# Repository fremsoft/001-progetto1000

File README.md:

# #progetto1000 il Robot che risolve il Cubo di Rubik
Questo è il primo progetto del [:arrow_forward: Canale YouTube "PROGETTI con Emanuele Frisoni"](https://youtube.com/c/fremsoft), un progetto collaborativo che nasce al raggiungimento di 1000 iscritti: [:movie_camera: Guarda la Playlist completa del progetto](https://www.youtube.com/watch?v=VcB0eAnL97o&list=PLxAafib4pWc7LSfuXC9RSEif6I1dyx5FP)

1. [Parte la progettazione in Live Streaming su Twitch](README.md#parte-la-progettazione-in-live-streaming-su-twitch)
2. [Definizione delle specifiche](README.md#definizione-delle-specifiche)
3. [Attività da svolgere e svolte](README.md#attivit%C3%A0-da-svolgere-e-svolte)
4. [Codici sorgenti](README.md#codici-sorgenti)
5. [Sostieni PROGETTO1000](README.md#sostieni-progetto1000)
6. [Lista della spesa](README.md#lista-della-spesa)

   6.1 [Attrezzature da laboratorio e Kit](README.md#attrezzature-da-laboratorio-e-kit)
   
   6.2 [Materiale e schede elettroniche](README.md#materiale-e-schede-elettroniche)
   
   6.3 [Materiale vario per assemblaggio prototipo](README.md#materiale-vario-per-assemblaggio-prototipo)

## Parte la progettazione in Live Streaming su Twitch
**Ogni Giovedì sera alle 22:00** ci incontriamo su [Twitch Tv](https://www.twitch.tv/fremsoft) per progettare insieme il Robot che risolve il Cubo di Rubik, partendo da zero. Affronteremo tutti i passaggi in maniera approfondita. Ho deciso di utilizzare tecnologie che conosco "per sentito dire", ma su cui non ho mai lavorato. In questo modo vedrai tutto il processo che sta dietro alla ricerca di una soluzione. A differenza di altri progetti che trovi in rete, #progetto1000 non esiste ancora, lo possiamo creare insieme. 

Lo scopo non è mostrare al mondo quanto siamo bravi, ma mostrare agli aspiranti progettisti quali sono tutte le difficoltà che potranno incontrare nel loro percorso e suggerire un modo per affrontarle e superarle.

:clapper: Canale Twitch:  [https://www.twitch.tv/fremsoft](https://www.twitch.tv/fremsoft)

[^ Torna su](README.md#progetto1000-il-robot-che-risolve-il-cubo-di-rubik)

## Definizione delle specifiche
Siccome si tratta di un progetto collaborativo, per definire le specifiche di progetto sono stati fatti alcuni sondaggi esplorativi per determinare quali tecnologie utilizzare in questo primo progetto. I risultati del sondaggio sono i seguenti:

1. Arduino o Microchip PIC? **ARDUINO** [4 voti / 2]

2. Encoder Ottico o Accelerometro Gravitazionale? **ENCODER OTTICO** [3 voti / 1]

3. Costruzioni LEGO o Particolari stampati con Stampante 3D? **STAMPA 3D** [3 voti / 4]

4. Stand alone o Connesso a un PC/Smartphone? **SIA STANDALONE CHE COMANDATO** [4 voti / 4]

5. Muto o Sonoro? **SONORO** [3 voti / 4]

6. Cieco o con Telecamera? **TELECAMERA** [0 voti / 4]

7. Procedurale o Intelligenza Artificiale? **A.I.** [0 voti / 5 ]

[^ Torna su](README.md#progetto1000-il-robot-che-risolve-il-cubo-di-rubik)

## Attività da svolgere e svolte
Ogni progetto che si rispetti deve prevedere una serie di fasi da svolgere. Maggiore sarà la difficoltà del progetto e maggiori sono le incognite, tanto più sarà difficile riuscire a prevedere con esattezza tutte le fasi. Ciononostante, è sempre buona norma prevedere con la massima accuratezza tutte le fasi del progetto in una sorta di planning. Ad ogni modo il progetto può essere periodicamente rivisitato, modificato e corretto, in corso d'opera.

L'utilità di suddividere il progetto in attività elementari, consente al progettista di avere un approccio più razionale ed evitare di disperdersi. Inoltre, laddove sia possibile lavorare in Team, la suddivisione del progetto in attività consente di stabilire se alcune attività possano essere svolte simultaneamente da più attori, per esempio dopo aver definito le specifiche di progetto con precisione, si può affidare il progetto meccanico ad un Team ed il progetto elettronico ad un altro Team di sviluppatori.

- [x] [Analisi di fattibilità](https://youtu.be/We6UntzGp7k)
- [x] Raccolta della documentazione e prove sperimentali con prototipi
  - [x] Dimensioni meccaniche e forze necessarie a manipolare il cubo di Rubik
  - [x] Caratteristiche elettriche e meccaniche dei motori c.c.
  - [x] Caratteristiche elettriche del driver (ponte-H) per motori c.c.
  - [x] Specifiche elettriche dei sensori ottici (fotoresistori/TCUT1350x01)
  - [x] Funzionamento di Arduino (uscite PWM, uscite parallele, timers)
  - [x] DAC e amplificatore audio per speaker 8 ohm
  - [x] Slot per Micro SD Card per Arduino per storage file audio
  - [x] Funzionamento Chip Camera OV7670 e acquisizione immagini
  - [x] Ottica del sensore OV7670
  - [x] Funzionamento del modulo WiFi per comunicazione con Smartphone
  - [x] Alimentazione 5V @ 10A
  - [-] ~~Selezione molle per mano robotica~~
- [x] Progettazione meccanica 
  - [x] Realizzazione delle parti che compongono il Robot (esportati in STL)
  - [x] Stampare in 3D le componenti meccaniche
  - [x] Assemblare le parti meccaniche con le parti elettriche (motori, encoder, etc)
- [x] Progettazione elettronica
   - [x] Alimentazione
   - [x] Shield p1000 
     - [x] DAC e Amplificatore per altoparlante
     - [x] Modulo SD-Card
     - [x] Interfacciamento Chip Camera OV7670
     - [x] Modulo WiFi
     - [x] Circuiti di condizionamento dei sensori ottici
     - [x] Comando motori
     - [x] Protezioni e filtri EMC/EMI
     - [x] Montare i componenti elettronici
     - [x] Collaudo generale dell'elettronica
- [ ] Progettazione del programma su Arduino
  - [ ] Movimentazione elementare (attraverso la porta seriale invieremo i comandi per eseguire i movimenti)
  - [ ] Acquisizione delle immagini da telecamera per distinguere i colori e mappare gli elementi del cubo di Rubik
  - [ ] Implementare gli algoritmi del metodo CFOP semplificato
    - [ ] Croce bianca
    - [ ] Faccia bianca e primo strato
    - [ ] Secondo strato
    - [ ] Croce gialla
    - [ ] OLL
    - [ ] PLL (primo passaggio)
    - [ ] PLL (secondo passaggio)
    - [ ] Allineamento terzo strato 
  - [ ] Implementare i suoni
- [ ] Progettazione della rete neurale
  - [ ] Addestramento di una rete neurale per riconoscere tutti gli OLL e PLL
  - [ ] Implementazione della rete neurale nell'algoritmo 
- [ ] Progettazione dell'applicativo per Android per mescolare il cubo con una specifica scramble o altro (forse questa fase salta)
- [ ] Dare un nome al robot

[^ Torna su](README.md#progetto1000-il-robot-che-risolve-il-cubo-di-rubik)

## Codici sorgenti
**#progetto1000** è un progetto Open-Source collaborativo. Tutti i sorgenti elaborati in fase di progettazione sono presenti su questo canale GitHub. Esplora le cartelle di [001-progetto1000](https://github.com/fremsoft/001-progetto1000) e troverai i sorgenti del progetto meccanico, elettronico, software e altro materiale prodotto in fase di progettazione.

Il codice sorgente di **Arduino** sarà disponibile anche a questo link: [Sorgenti Arduino](https://create.arduino.cc/editor/fremsoft/6501effc-6729-46f5-a2f1-0bfa0e9eb691/preview)

La Shield #P1000 è stata omaggiata da [PcbWay.com](https://www.pcbway.com/setinvite.aspx?inviteid=15084) che è sponsor ufficiale di Progetto 1000. Trovi il progetto del PCB scaricabile anche qui: [Shield #P1000 su PcbWay](https://www.pcbway.com/project/shareproject/Shield__P1000__for_Arduino_Mega.html), ricordati di votare il progetto!

[^ Torna su](README.md#progetto1000-il-robot-che-risolve-il-cubo-di-rubik)

## Sostieni PROGETTO1000 
Se **#progetto1000** ti sta appassionando e desideri sostenere la progettazione, puoi acquistare i componenti necessari alla creazione del prototipo o le attrezzature necessarie all'allestimento del laboratorio, facendoli recapitare al mio indirizzo. La lista dei desideri completa dove trovi tutte le cose che servono:

:notebook: "Wish list Amazon" - https://amzn.to/2BDtwIV

Un altro modo per sostenere il canale è seguendo il [canale YouTube](https://youtube.com/c/fremsoft), semplicemente guardando i video, iscrivendoti al canale, mettendo like e interagendo con i commenti, ma soprattutto condividendo i video che preferisci con i tuoi amici progettisti, sono tutti modi per sostenere gratuitamente il canale.

[^ Torna su](README.md#progetto1000-il-robot-che-risolve-il-cubo-di-rubik)

## Lista della spesa
**#progetto1000** sta nascendo, non abbiamo ancora una BOM (Bill Of Material), ma stiamo già acquistando un po' di materiale per realizzare il prototipo e fare le prime prove pratiche. Se vuoi sviluppare insieme a noi e vuoi eseguire le stesse prove a casa tua, ti indico quale materiale ho acquistato qui di seguito:

### Attrezzature da laboratorio e Kit
* [Kit Elettronico con breadboard](https://amzn.to/2QTgOw7)
* [Super Starter Kit UNO project](https://amzn.to/2QJrnNc)
* [Calibro digitale](https://amzn.to/36QMR6w)
* [Bilancia digitale](https://amzn.to/3nxseCa)

### Materiale e schede elettroniche
* [Arduino Mega 2560](https://amzn.to/30RCvj6)
* [Telecamera a colori per Arduino](https://amzn.to/3nbS0Ma)
* [Set 6 motori con accessori](https://amzn.to/3nhQrfy)
* [Fotoresistore](https://amzn.to/370EtBg)
* [Shield #P1000 su PcbWay](https://www.pcbway.com/project/shareproject/Shield__P1000__for_Arduino_Mega.html)

### Materiale vario per assemblaggio prototipo
* [Sfere in acciaio 4mm](https://amzn.to/3lzfDwr)

Trovi la lista completa al seguente link:
🛒 [Lista della spesa di #progetto1000](https://www.amazon.it/hz/wishlist/ls/8D7WPLCAZ7KL?tag=p-ef-21)

[^ Torna su](README.md#progetto1000-il-robot-che-risolve-il-cubo-di-rubik)

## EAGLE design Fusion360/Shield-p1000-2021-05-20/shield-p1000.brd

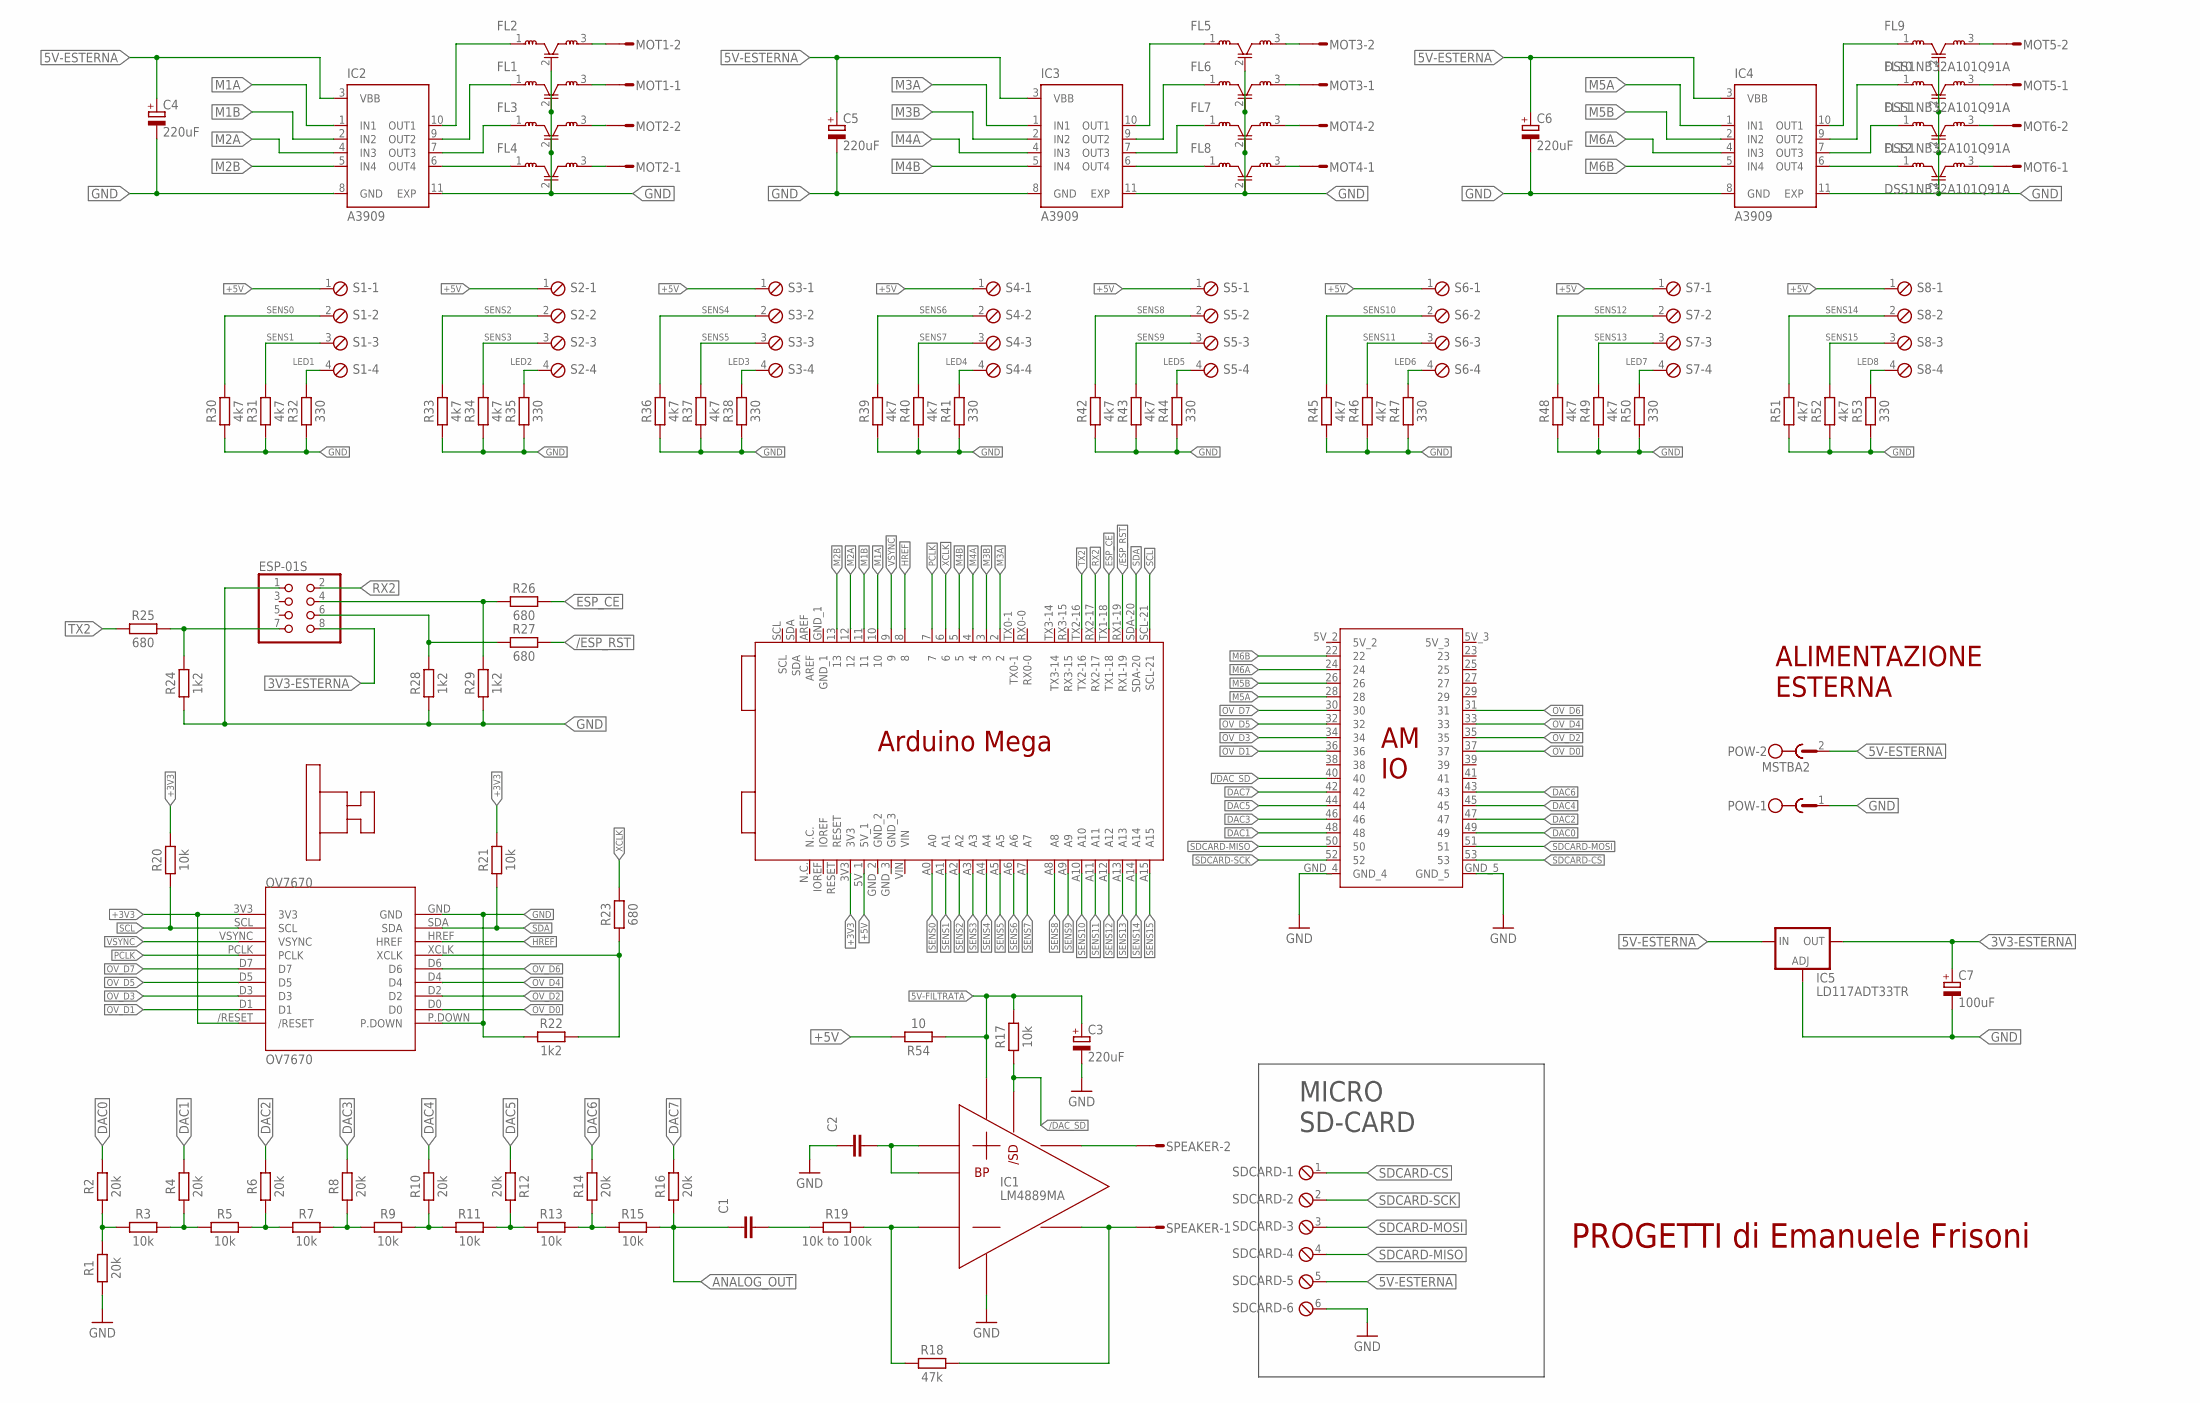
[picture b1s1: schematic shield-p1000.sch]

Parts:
ARDUINO-MEGA1: ARDUINO-MEGA-SH
C1, C2: 1uF; CAPC1608X85
C3, C4, C5, C6: 220uF; E3,5-10
C7: 100uF; E3,5-10
ESP-01S: PINHD-2X4; 2X04
FL1, FL2, FL3, FL4, FL5, FL6, FL7, FL8, FL9, FL10, FL11, FL12: DSS1NB32A101Q91A; RADIAL-3
IC1: LM4889MA; SOIC127P599X175-8N
IC2, IC3, IC4: A3909; 10-MSOP
IC5: LD117ADT33TR; DPACK
MOT1, MOT2, MOT3, MOT4, MOT5, MOT6: S02P
OV7670: OV7670; OV7670-HEADER
POW: MSTBA2
R1, R2, R4, R6, R8, R10, R12, R14, R16: 20k; RESC1608X60
R3, R5, R7, R9, R11, R13, R15, R17, R20, R21: 10k; RESC1608X60
R18: 47k; RESC1608X60
R19: 10k to 100k; RESAD724W46L381D178B
R22, R24, R28, R29: 1k2; RESC1608X60
R23, R25, R26, R27: 680; RESC1608X60
R30, R31, R33, R34, R36, R37, R39, R40, R42, R43, R45, R46, R48, R49, R51, R52: 4k7; RESC1608X60
R32, R35, R38, R41, R44, R47, R50, R53: 330; RESC1608X60
R54: 10; RESC1608X60
S1, S2, S3, S4, S5, S6, S7, S8: MPT4; 4POL254
SDCARD: MPT6; 6POL254
SPEAKER: S02P

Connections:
3V3-ESTERNA: C7.+, ESP-01S.8, IC5.4 (OUT)
5V-ESTERNA: C4.+, C5.+, C6.+, IC2.3 (VBB), IC3.3 (VBB), IC4.3 (VBB), IC5.3 (IN), POW.2, SDCARD.5
5V-FILTRATA: C3.+, IC1.6 (VDD), R17.1, R54.2
+3V3: ARDUINO-MEGA1.3V3, OV7670.3V3, OV7670./RESET, R20.2, R21.2
+5V: ARDUINO-MEGA1.5V_1, R54.1, S1.1, S2.1, S3.1, S4.1, S5.1, S6.1, S7.1, S8.1
/DAC_SD: ARDUINO-MEGA1.40, IC1.1 (/SHUTDOWN), R17.2
/ESP_RST: ARDUINO-MEGA1.RX1-19, R27.2
ANALOG_OUT: C1.1, R15.1, R16.2
DAC0: ARDUINO-MEGA1.49, R2.1
DAC1: ARDUINO-MEGA1.48, R4.1
DAC2: ARDUINO-MEGA1.47, R6.1
DAC3: ARDUINO-MEGA1.46, R8.1
DAC4: ARDUINO-MEGA1.45, R10.1
DAC5: ARDUINO-MEGA1.44, R12.1
DAC6: ARDUINO-MEGA1.43, R14.1
DAC7: ARDUINO-MEGA1.42, R16.1
ESP_CE: ARDUINO-MEGA1.TX1-18, R26.2
GND: ARDUINO-MEGA1.GND_4, ARDUINO-MEGA1.GND_5, C2.1, C3.-, C4.-, C5.-, C6.-, C7.-, ESP-01S.1, FL1.2 (GND), FL2.2 (GND), FL3.2 (GND), FL4.2 (GND), FL5.2 (GND), FL6.2 (GND), FL7.2 (GND), FL8.2 (GND), FL9.2 (GND), FL10.2 (GND), FL11.2 (GND), FL12.2 (GND), IC1.7 (VSS), IC2.8 (GND), IC2.11 (EXP), IC3.8 (GND), IC3.11 (EXP), IC4.8 (GND), IC4.11 (EXP), IC5.1 (ADJ), OV7670.GND, OV7670.P.DOWN, POW.1, R1.1, R22.1, R24.1, R28.1, R29.1, R30.1, R31.1, R32.1, R33.1, R34.1, R35.1, R36.1, R37.1, R38.1, R39.1, R40.1, R41.1, R42.1, R43.1, R44.1, R45.1, R46.1, R47.1, R48.1, R49.1, R50.1, R51.1, R52.1, R53.1, SDCARD.6
HREF: ARDUINO-MEGA1.8, OV7670.HREF
LED1: R32.2, S1.4
LED2: R35.2, S2.4
LED3: R38.2, S3.4
LED4: R41.2, S4.4
LED5: R44.2, S5.4
LED6: R47.2, S6.4
LED7: R50.2, S7.4
LED8: R53.2, S8.4
M1A: ARDUINO-MEGA1.10, IC2.1 (IN1)
M1B: ARDUINO-MEGA1.11, IC2.2 (IN2)
M2A: ARDUINO-MEGA1.12, IC2.4 (IN3)
M2B: ARDUINO-MEGA1.13, IC2.5 (IN4)
M3A: ARDUINO-MEGA1.2, IC3.1 (IN1)
M3B: ARDUINO-MEGA1.3, IC3.2 (IN2)
M4A: ARDUINO-MEGA1.4, IC3.4 (IN3)
M4B: ARDUINO-MEGA1.5, IC3.5 (IN4)
M5A: ARDUINO-MEGA1.28, IC4.1 (IN1)
M5B: ARDUINO-MEGA1.26, IC4.2 (IN2)
M6A: ARDUINO-MEGA1.24, IC4.4 (IN3)
M6B: ARDUINO-MEGA1.22, IC4.5 (IN4)
unnamed: R1.2, R2.2, R3.2
unnamed: R3.1, R4.2, R5.2
unnamed: R5.1, R6.2, R7.2
unnamed: R7.1, R8.2, R9.2
unnamed: R9.1, R10.2, R11.2
unnamed: R11.1, R12.2, R13.2
unnamed: R13.1, R14.2, R15.2
unnamed: IC1.8 (VO2), SPEAKER.2
unnamed: FL4.1, IC2.6 (OUT4)
unnamed: C1.2, R19.1
unnamed: IC1.4 (IN-), R18.2, R19.2
unnamed: IC1.5 (VO1), R18.1, SPEAKER.1
unnamed: C2.2, IC1.2 (BYPASS), IC1.3 (IN+)
unnamed: ESP-01S.7, R24.2, R25.2
unnamed: ESP-01S.4, R26.1, R29.2
unnamed: ESP-01S.6, R27.1, R28.2
unnamed: FL3.1, IC2.7 (OUT3)
unnamed: FL1.1, IC2.9 (OUT2)
unnamed: FL2.1, IC2.10 (OUT1)
unnamed: FL2.3, MOT1.2
unnamed: FL1.3, MOT1.1
unnamed: FL3.3, MOT2.2
unnamed: FL4.3, MOT2.1
unnamed: FL8.1, IC3.6 (OUT4)
unnamed: FL7.1, IC3.7 (OUT3)
unnamed: FL6.1, IC3.9 (OUT2)
unnamed: FL5.1, IC3.10 (OUT1)
unnamed: FL5.3, MOT3.2
unnamed: FL6.3, MOT3.1
unnamed: FL7.3, MOT4.2
unnamed: FL8.3, MOT4.1
unnamed: FL12.1, IC4.6 (OUT4)
unnamed: FL11.1, IC4.7 (OUT3)
unnamed: FL10.1, IC4.9 (OUT2)
unnamed: FL9.1, IC4.10 (OUT1)
unnamed: FL9.3, MOT5.2
unnamed: FL10.3, MOT5.1
unnamed: FL11.3, MOT6.2
unnamed: FL12.3, MOT6.1
OV_D0: ARDUINO-MEGA1.37, OV7670.D0
OV_D1: ARDUINO-MEGA1.36, OV7670.D1
OV_D2: ARDUINO-MEGA1.35, OV7670.D2
OV_D3: ARDUINO-MEGA1.34, OV7670.D3
OV_D4: ARDUINO-MEGA1.33, OV7670.D4
OV_D5: ARDUINO-MEGA1.32, OV7670.D5
OV_D6: ARDUINO-MEGA1.31, OV7670.D6
OV_D7: ARDUINO-MEGA1.30, OV7670.D7
PCLK: ARDUINO-MEGA1.7, OV7670.PCLK
RX2: ARDUINO-MEGA1.RX2-17, ESP-01S.2
SCL: ARDUINO-MEGA1.SCL-21, OV7670.SCL, R20.1
SDA: ARDUINO-MEGA1.SDA-20, OV7670.SDA, R21.1
SDCARD-CS: ARDUINO-MEGA1.53, SDCARD.1
SDCARD-MISO: ARDUINO-MEGA1.50, SDCARD.4
SDCARD-MOSI: ARDUINO-MEGA1.51, SDCARD.3
SDCARD-SCK: ARDUINO-MEGA1.52, SDCARD.2
SENS0: ARDUINO-MEGA1.A0, R30.2, S1.2
SENS1: ARDUINO-MEGA1.A1, R31.2, S1.3
SENS2: ARDUINO-MEGA1.A2, R33.2, S2.2
SENS3: ARDUINO-MEGA1.A3, R34.2, S2.3
SENS4: ARDUINO-MEGA1.A4, R36.2, S3.2
SENS5: ARDUINO-MEGA1.A5, R37.2, S3.3
SENS6: ARDUINO-MEGA1.A6, R39.2, S4.2
SENS7: ARDUINO-MEGA1.A7, R40.2, S4.3
SENS8: ARDUINO-MEGA1.A8, R42.2, S5.2
SENS9: ARDUINO-MEGA1.A9, R43.2, S5.3
SENS10: ARDUINO-MEGA1.A10, R45.2, S6.2
SENS11: ARDUINO-MEGA1.A11, R46.2, S6.3
SENS12: ARDUINO-MEGA1.A12, R48.2, S7.2
SENS13: ARDUINO-MEGA1.A13, R49.2, S7.3
SENS14: ARDUINO-MEGA1.A14, R51.2, S8.2
SENS15: ARDUINO-MEGA1.A15, R52.2, S8.3
TX2: ARDUINO-MEGA1.TX2-16, R25.1
VSYNC: ARDUINO-MEGA1.9, OV7670.VSYNC
XCLK: ARDUINO-MEGA1.6, R23.2
XCLK1: OV7670.XCLK, R22.2, R23.1

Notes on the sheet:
MICRO SD-CARD
ALIMENTAZIONE ESTERNA
PROGETTI di Emanuele Frisoni

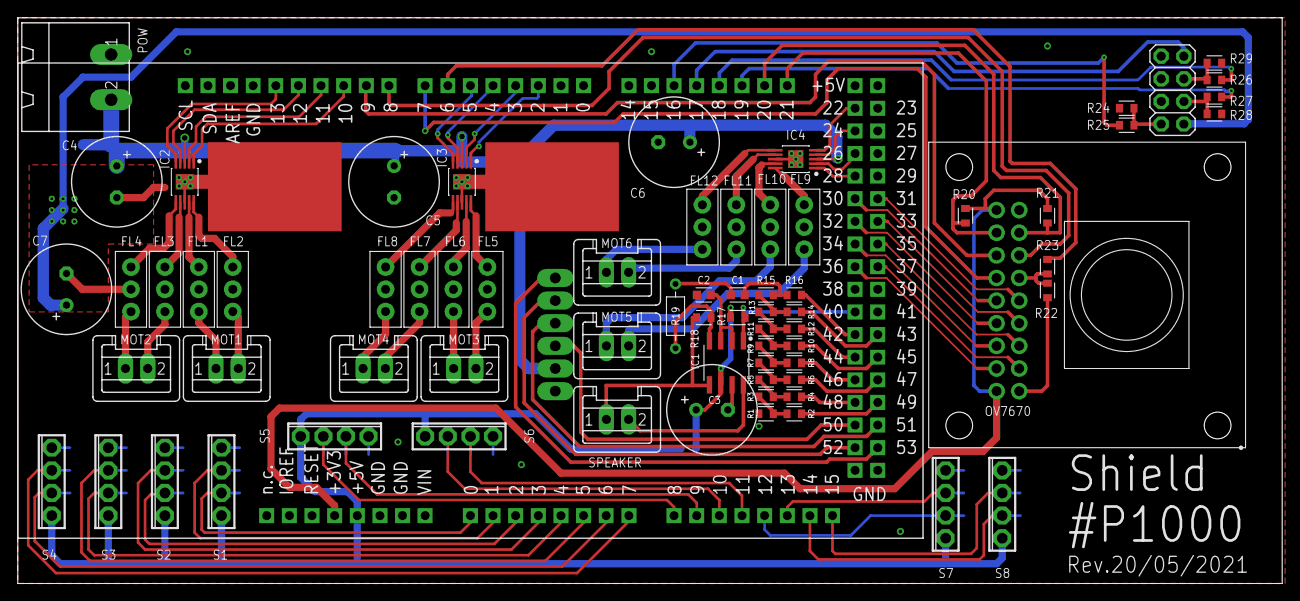
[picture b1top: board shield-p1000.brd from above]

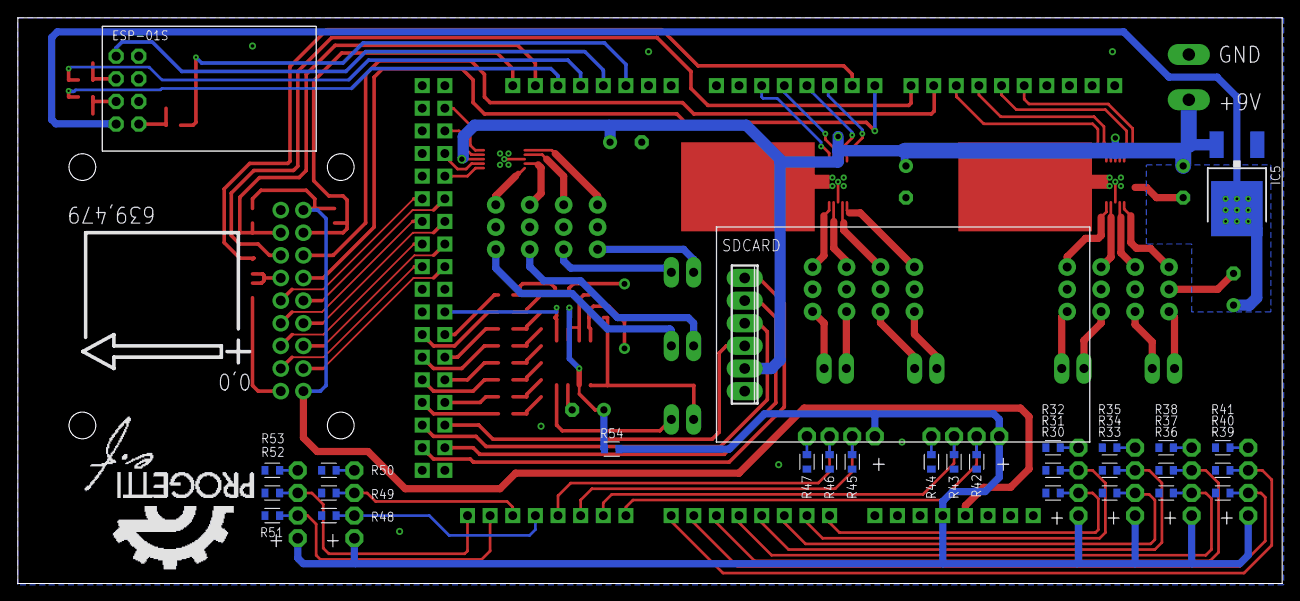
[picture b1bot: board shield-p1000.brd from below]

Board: 2 copper layers, 141.9 x 63.5 mm, 98 parts (27 on the bottom side), 114 nets.

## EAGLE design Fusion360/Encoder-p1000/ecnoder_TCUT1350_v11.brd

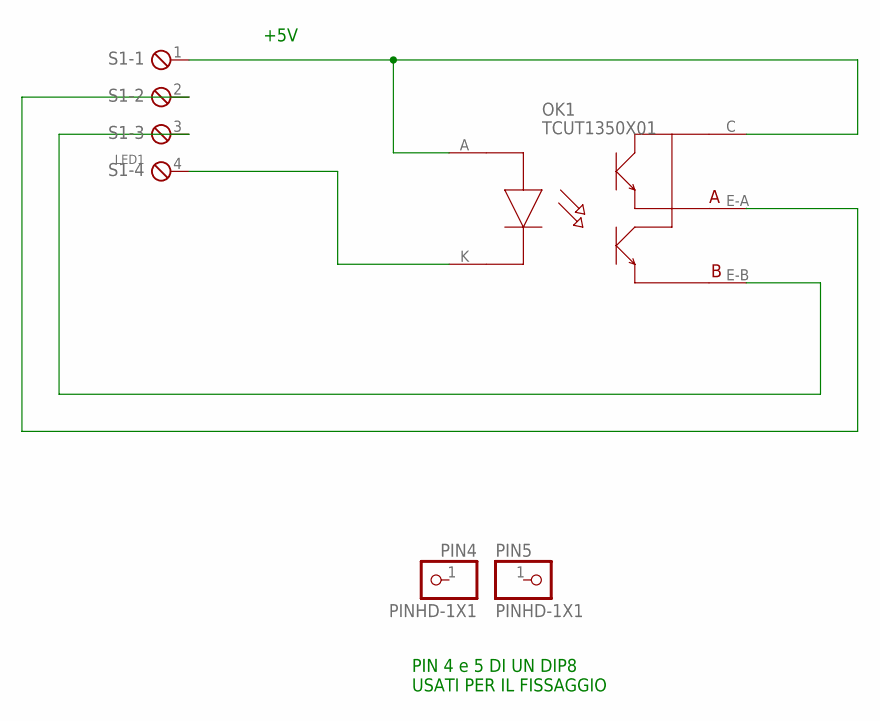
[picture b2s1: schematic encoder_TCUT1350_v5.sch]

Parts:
OK1: TCUT1350X01
PIN4, PIN5: PINHD-1X1; 1X01
S1: MPT4; 4POL254

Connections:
+5V: OK1.A, OK1.C, S1.1
LED1: OK1.K, S1.4
unnamed: OK1.E-B, S1.3
unnamed: OK1.E-A, S1.2

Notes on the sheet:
+5V
PIN 4 e 5 DI UN DIP8 USATI PER IL FISSAGGIO

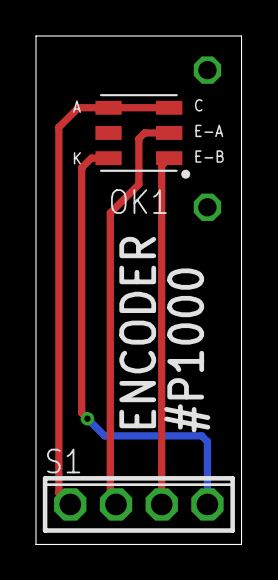
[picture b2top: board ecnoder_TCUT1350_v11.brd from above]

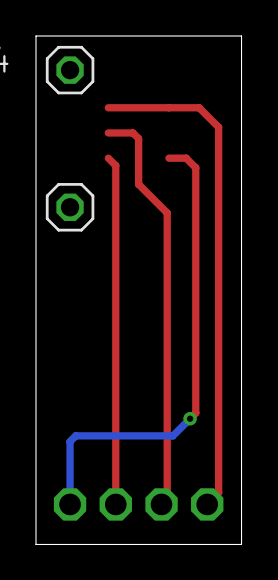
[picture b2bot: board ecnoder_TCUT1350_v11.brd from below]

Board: 2 copper layers, 11.4 x 28.2 mm, 4 parts (2 on the bottom side), 4 nets.

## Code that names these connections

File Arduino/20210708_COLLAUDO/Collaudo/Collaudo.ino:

/*
  SD card file dump

  This example shows how to read a file from the SD card using the
  SD library and send it over the serial port.

  The circuit:
   SD card attached to SPI bus as follows:
 ** MOSI - pin 11 (UNO) / 51 (MEGA)
 ** MISO - pin 12 (UNO) / 50 (MEGA)
 ** CLK -  pin 13 (UNO) / 52 (MEGA)
 ** CS -   pin 10 (UNO) / 53 (MEGA)  [(for MKRZero SD: SDCARD_SS_PIN)]

  Appunti:
 ** https://www.arduino.cc/en/Hacking/PinMapping2560
 ** https://www.arduino.cc/en/reference/SPI
 ** https://www.arduino.cc/en/reference/SD
   
  created  22 December 2010
  by Limor Fried
  modified 9 Apr 2012
  by Tom Igoe

  riadattato il 17 Dicembre 2020
  per Progetto1000 da Emanuele Frisoni
  
  Guarda il video: https://www.youtube.com/watch?v=kRmUnPmCAZg

  This example code is in the public domain.
*/

#include <SPI.h>
#include <SD.h>

#define  DEBUG_PIN             8

#define  CSPIN                53    /* per Arduino Mega il default è 53 */
#define  DAC_SHUT_DOWN        40
#define  NOMEFILE  "datalog.txt"

#define  MOT1A                10
#define  MOT1B                11
#define  MOT2A                12
#define  MOT2B                13

#define  MOT3A                2
#define  MOT3B                3
#define  MOT4A                4
#define  MOT4B                5

#define  MOT5A                28
#define  MOT5B                26
#define  MOT6A                24
#define  MOT6B                22

#define  SENS0                A0
#define  SENS1                A1
#define  SENS2                A2
#define  SENS3                A3
#define  SENS4                A4
#define  SENS5                A5
#define  SENS6                A6
#define  SENS7                A7
#define  SENS8                A8
#define  SENS9                A9
#define  SENS10               A10
#define  SENS11               A11
#define  SENS12               A12
#define  SENS13               A13
#define  SENS14               A14
#define  SENS15               A15


volatile signed int vel_mot1;       /* velocita va da -100 a +100 */


#define SIZE_CIRCULAR_BUFFER 64
#define MASK_CIRCULAR_BUFFER 0x3F

volatile unsigned char circular_buffer[ SIZE_CIRCULAR_BUFFER ];
volatile unsigned char circular_buffer_head, circular_buffer_tail, circular_buffer_len;

void mio_delay(int msec);
void play_something(char * nomefile);


void setup() {
  /* Open serial communications and wait for port to open: */
  Serial.begin(115200);
  
  while (!Serial) {
    /* wait for serial port to connect. Needed for native USB port only */
    /* do nothing */;    
  }

#if FALSE
  Serial.print("Initializing SD card...");

  // see if the card is present and can be initialized:
  if (!SD.begin(CSPIN)) {
    
    Serial.println("Card failed, or not present");
    while (1); 
    
  }
  
  Serial.println("card initialized.");
#endif

  /* inizializzazione buffer circolare */
  circular_buffer_head = 0;
  circular_buffer_tail = 0;
  circular_buffer_len  = 0;

  /* impostazione Timer 3 per dare 
   * un interrupt a 8ksps ogni 125 uSec
   * Quarzo = 16MHz; 62,5 nSec ---> 2000 impulsi ogni 125 uSec
   */
  cli();
  TCCR5A = 0x00;
  // prescaler 
  TCCR5B = 0x01;    /* modalità Clear Timer on Compare Match e senza prescaler */
  // conteggio da raggiungere
  OCR5A = (2000 - 1);
  // attivo CTC Mode
  TCCR5B |= 0x08;
  // abilita interrupt on match counter
  TIMSK5 = 0x02;
  sei();

  pinMode(DAC_SHUT_DOWN, OUTPUT); /* ABILITAZIONE AMPLIFICATORE ATTIVO BASSO */ 
  digitalWrite( DAC_SHUT_DOWN, LOW );
  
  /* PORT-L PINS per DAC */
  pinMode(42, OUTPUT); /* PORT - L7 - Most Significant bit */ 
  pinMode(43, OUTPUT);
  pinMode(44, OUTPUT);
  pinMode(45, OUTPUT);
  pinMode(46, OUTPUT);
  pinMode(47, OUTPUT);
  pinMode(48, OUTPUT);
  pinMode(49, OUTPUT); /* PORT - L0 - Least Significant bit*/ 
  PORTL = 128;
   

#ifdef DEBUG_MODE 
  pinMode( DEBUG_PIN , OUTPUT); 
#endif

  //play_something( "audio/track001.raw" );
  //play_something( "audio/track002.raw" );

  pinMode(MOT1A, OUTPUT); 
  pinMode(MOT1B, OUTPUT); 
  digitalWrite( MOT1A, HIGH );
  digitalWrite( MOT1B, HIGH );
  vel_mot1 = 50;
  
}

void loop() {

  static unsigned long t1 = millis(), t2;
  static int inversione = 1;
  static int passi = 0, stato = 0;

  /*
   
   Serial.print ( "0," );
   Serial.print ( analogRead( SENS0 ) );
   Serial.print ( "," );
   Serial.println ( analogRead( SENS1 ) );
  
  */

  /*
   CALCOLO RPM
   
  while ( digitalRead(SENS15) == 0 ) /* do nothing * /;

  t2 = 60000000UL / (micros() - t1);
  t1 = micros();

  while ( digitalRead(SENS15) == 1 ) /* do nothing * /;

  Serial.println ( t2 );
  */

  /* 
   *  CONTEGGIO PASSI
   *  
   */
   switch( stato )
   {

//  stato   0   1   2   3   0 
//   14     0   1   1   0   0
//   15     0   0   1   1   0

    case 0: 
      if ( digitalRead(SENS14) == 1) { stato = 1; }
      if ( digitalRead(SENS15) == 1) { stato = 3; }
      break;    
       
    case 1: 
      if ( digitalRead(SENS14) == 0) { stato = 0; passi --; }
      if ( digitalRead(SENS15) == 1) { stato = 2; }
      break;    
    
    case 2: 
      if ( digitalRead(SENS14) == 0) { stato = 3; }
      if ( digitalRead(SENS15) == 0) { stato = 1; }
      break;    

    case 3: 
      if ( digitalRead(SENS14) == 1) { stato = 2; }
      if ( digitalRead(SENS15) == 0) { stato = 0; passi++; }
      break;    
    
   }

   t2 = (millis() - t1);
   if (t2 >= 100) 
   {
     t1 = millis();
     Serial.println ( passi );

     inversione --; 
     if (inversione <= 0) 
     {
       if (vel_mot1 == 50) 
         { vel_mot1 = -50; }
       else 
         { vel_mot1 = 50; }
     
       inversione = 100;
     }
   }

}

void loop1() {

  Serial.println("Motore Avanti");

  vel_mot1 = 30;

  while (vel_mot1 < 80) {
    mio_delay(50);
    vel_mot1 ++;
  }

  mio_delay(2000);

  while (vel_mot1 > 30) {
    mio_delay(50);
    vel_mot1 --;
  }

  vel_mot1 = 0;
  mio_delay(2000);


  Serial.println("Motore Indietro");

  vel_mot1 = -30;

  while (vel_mot1 > -80) {
    mio_delay(50);
    vel_mot1 --;
  }

  mio_delay(2000);

  while (vel_mot1 < -30) {
    mio_delay(50);
    vel_mot1 ++;
  }
  
  vel_mot1 = 0;
  mio_delay(2000);

}

void mio_delay(int msec)
{
  unsigned long t;

  t = millis() + msec;
  while (millis() < t) { /* do_nothing */ } 

}

void play_something( const char * nomefile )
{
  /* open the file. note that only one file can be open at a time,
   * so you have to close this one before opening another.
   */
  File dataFile = SD.open( nomefile );
  int c;

  if (dataFile) {

    digitalWrite( DAC_SHUT_DOWN, HIGH );
  
    /* if the file is present, send its content on the serial line for debug */
    while (dataFile.available()) { 

      while (circular_buffer_len >= (SIZE_CIRCULAR_BUFFER - 1)) /* do nothing */;
      
      c = dataFile.read();

      // Debug: Serial.println( c );

      circular_buffer[ circular_buffer_head ] = c;
      circular_buffer_head = (circular_buffer_head + 1) & MASK_CIRCULAR_BUFFER; 
      circular_buffer_len ++;
      
    }
    
    /* close file when finished */
    dataFile.close();

    digitalWrite( DAC_SHUT_DOWN, LOW );
  }
  else {

    /* if the file isn't open, pop up an error: */
    Serial.println("error opening ");
    Serial.println( nomefile );
      
  }
}

#ifdef DEBUG_MODE 
volatile int debug_var;
#endif

/* TIMER 3 COMPARE MATCH INTERRUPT OGNI 125 uSEC = 8 Ksps */
ISR(TIMER5_COMPA_vect) {
  static int contatore_pwm = 0;
  
#ifdef DEBUG_MODE 
   if (debug_var != 0) {
     debug_var = 0;
     digitalWrite( DEBUG_PIN , LOW );
   }
   else {
     debug_var = 1;
     digitalWrite( DEBUG_PIN , HIGH );
   }
#endif

   /* GESTIONE DAC */
   if (circular_buffer_len > 0)
   {
      PORTL = circular_buffer[ circular_buffer_tail ];
      
      circular_buffer_tail = (circular_buffer_tail + 1) & MASK_CIRCULAR_BUFFER; 
      circular_buffer_len --;
   }

   /* GESTIONE PWM MOTORI */
   contatore_pwm++; if (contatore_pwm >= 100) { contatore_pwm = 0; }
   if (vel_mot1 > 0)
   {
     /* il motore deve girare in avanti - orario */
     digitalWrite( MOT1A, ((vel_mot1 >= contatore_pwm)?(LOW):(HIGH)) );
     digitalWrite( MOT1B, HIGH );
   }
   else if (vel_mot1 < 0)
   {
     /* il motore deve girare indietro - antiorario*/
     digitalWrite( MOT1A, HIGH );
     digitalWrite( MOT1B, ((abs(vel_mot1) >= contatore_pwm)?(LOW):(HIGH)) );
   }
   else
   {
     /* il motore deve stare fermo */
     digitalWrite( MOT1A, HIGH );
     digitalWrite( MOT1B, HIGH );
   }
      
}

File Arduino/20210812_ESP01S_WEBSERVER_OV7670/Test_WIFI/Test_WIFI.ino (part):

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 *  15-04-2021 - Emanuele Frisoni
 */

#define ESP_CE    18
#define ESP_RST   19

char ch;         // Il canale del chiamante
int  n_to_rcv;   // Numero di byte da ricevere
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
/*  INDIRIZZO DELLA CHIP CAMERA OV7670 */
#define SCCB_ADDRESS  0x21
/*  7 PCLK - PH4  0001 0000  0x10
 *  8 HREF - PH5  0010 0000  0x20
 *  9 VREF - PH6  0100 0000  0x40
 **/
#define OV7670_PIXEL_CLOCK (PINH & 0b00010000)   // PIN 7
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#define REG_COM4            0x0d  /* Control 4 */
#define REG_COM5            0x0e  /* All "reserved" */
#define REG_COM6            0x0f  /* Control 6 */
#define COM6_HREF_HB        0x80  /* Suppress PCLK on horiz blank */
#define REG_AECH            0x10  /* More bits of AEC value */
#define REG_CLKRC           0x11  /* Clocl control */
#define CLK_EXT             0x40  /* Use external clock directly */
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#define COM8_AEC            0x01  /* Auto exposure enable */
#define REG_COM9            0x14  /* Control 9- gain ceiling */
#define REG_COM10           0x15  /* Control 10 */
#define COM10_HSYNC         0x40  /* HSYNC instead of HREF */
#define COM10_PCLK_HB       0x20  /* Suppress PCLK on horiz blank */
#define COM10_PCLK_REV      0x10  /* Reverse PCLK */
#define COM10_HREF_REV      0x08  /* Reverse HREF */
#define COM10_VS_LEAD       0x04  /* VSYNC on clock leading edge */
#define COM10_VS_NEG        0x02  /* VSYNC negative */
#define COM10_HS_NEG        0x01  /* HSYNC negative */
#define REG_HSTART          0x17  /* Horiz start high bits */
#define REG_HSTOP           0x18  /* Horiz stop high bits */
#define REG_VSTART          0x19  /* Vert start high bits */
#define REG_VSTOP           0x1a  /* Vert stop high bits */
#define REG_PSHFT           0x1b  /* Pixel delay after HREF */
#define REG_MIDH            0x1c  /* Manuf. ID high */
#define REG_MIDL            0x1d  /* Manuf. ID low */
#define REG_MVFP            0x1e  /* Mirror / vflip */
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#define REG_VPT             0x26  /* AGC/AEC fast mode op region */
#define REG_HSYST           0x30  /* HSYNC rising edge delay */
#define REG_HSYEN           0x31  /* HSYNC falling edge delay */
#define REG_HREF            0x32  /* HREF pieces */
#define REG_TSLB            0x3a  /* lots of stuff */
#define TSLB_YLAST          0x04  /* UYVY or VYUY - see com13 */
#define REG_COM11           0x3b  /* Control 11 */
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#define COM11_50HZ          0x08  /* Manual 50Hz select */
#define COM11_EXP           0x02
#define REG_COM12           0x3c  /* Control 12 */
#define COM12_HREF          0x80  /* HREF always */
#define REG_COM13           0x3d  /* Control 13 */
#define COM13_GAMMA         0x80  /* Gamma enable */
#define COM13_UVSAT         0x40  /* UV saturation auto adjustment */
#define COM13_UVSWAP        0x01  /* V before U - w/TSLB */
#define REG_COM14           0x3e  /* Control 14 */
#define COM14_DCWEN         0x10  /* DCW/PCLK-scale enable */
#define REG_EDGE            0x3f  /* Edge enhancement factor */
#define REG_COM15           0x40  /* Control 15 */
#define COM15_R10F0         0x00  /* Data range 10 to F0 */
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#define COM7_YUV            0x00  /* YUV */
#define COM7_BAYER          0x01  /* Bayer format */
#define COM7_PBAYER         0x05  /* "Processed bayer" */
#define COM10_VS_LEAD       0x04  /* VSYNC on clock leading edge */
#define COM11_50HZ          0x08  /* Manual 50Hz select */
#define COM13_UVSAT         0x40  /* UV saturation auto adjustment */
#define COM15_R01FE         0x80  /*      01 to FE */
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  /* Sul pin 4 di Arduino Mega è stato collegato il Reset di ESP-01S 
   *  attivo basso (0 = RESET) sempre attraverso il partitore resistivo 
   *  680/1200 ohm per trasformare i segnali a 5V in 3V */
  pinMode(ESP_RST, OUTPUT);  // RESET
  digitalWrite(ESP_RST, HIGH);  

  pinMode(ESP_CE, OUTPUT);  // RESET
  digitalWrite(ESP_CE, HIGH);  

  /* Impostazione della seriale di servizio per il debug */
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  OCR4A = 0;

  // CONFIGURO I PIN 7-8-9 COME INGRESSI
  pinMode(7, INPUT);  //PCLK - PH4
  pinMode(8, INPUT);  //HREF - PH5
  pinMode(9, INPUT);  //VREF - PH6
    
  // CONFIGURO I PIN 30-37 COME INGRESSI
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
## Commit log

2020-10-17 dOCUMENTAZIONE ov7670
2020-10-19 OV7670 Datasheet
2020-11-01 Motorino DC 3V
2020-11-05 datasheet
2020-11-28 AUDIO SPECIFICATIONS
2020-12-06 TEST DAC
2020-12-08 Wi-Fi
2020-12-21 Test DAC con WAV
2020-12-21 Test Micro SD Card reader
2020-12-21 Test DAC con Wave
2020-12-21 Test SD Card
2021-01-17 Schematic & Library
2021-01-17 Doc Arduino
2021-02-05 DAC e Sintetizzatore Audio
2021-02-05 CK 8MHz
2021-02-05 DAC WAV
2021-02-05 DAC Generatore di funzioni
2021-02-05 Hello World P1000
2021-02-05 DAC file WAV
2021-02-05 Play Wav from SD Card
2021-02-05 Generate 8MHz Clock
2021-02-28 OV7670 Capture
2021-03-12 indrek
2021-03-12 altre prove
2021-03-14 minimal changes
2021-03-16 Rename read.me to README.md
2021-03-18 Prove Ottica OV7670
2021-03-28 pinC
2021-03-28 PIN C INPUT
2021-04-09 wifi doc
2021-04-13 DOC ESP-01S
2021-04-18 WebServer con Arduino Mega e ESP-01S
2021-05-08 WiFi module AZ-Delivery
2021-05-20 GERBER FILES #P1000
2021-06-12 FOTO PCB
2021-06-17 Dataskeet
2021-09-23 Modifiche al PCB
2021-10-28 prima prova di mano robotica
2021-11-04 Aggiornamento 04-11-2021
2021-11-18 Aggiunto terzo dito
2021-11-25 encoder rotazione mano
2021-12-09 aggiornamento 9-12-2021
2021-12-16 modifiche 16 dicembre 2021
2021-12-23 Aggiunto encoder
2022-01-13 Definitivo v60
2022-01-13 Mano definitiva v60
2022-01-20 v65
    Aumentato spessore della parete esterna
2022-02-10 10-02-2022
2022-02-25 Completo carter
2022-02-25 Complessivo
2022-03-10 allargata fessura ingranaggio
2022-06-23 con cuscinetti
2022-08-07 collaudo
2022-10-06 ENCODER-P1000
2023-01-12 Joystick
2024-06-17 Collaudo 1
2024-07-01 collaudo 3
2024-07-08 ENCODER MANO
2024-07-15 Apre Chiude mani
2024-08-26 Rev6
